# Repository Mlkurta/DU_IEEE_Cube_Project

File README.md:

# DU_IEEE_Cube_Project
Repo for Sharing of files, templates and code for an 8x8x8 RGB LED cube

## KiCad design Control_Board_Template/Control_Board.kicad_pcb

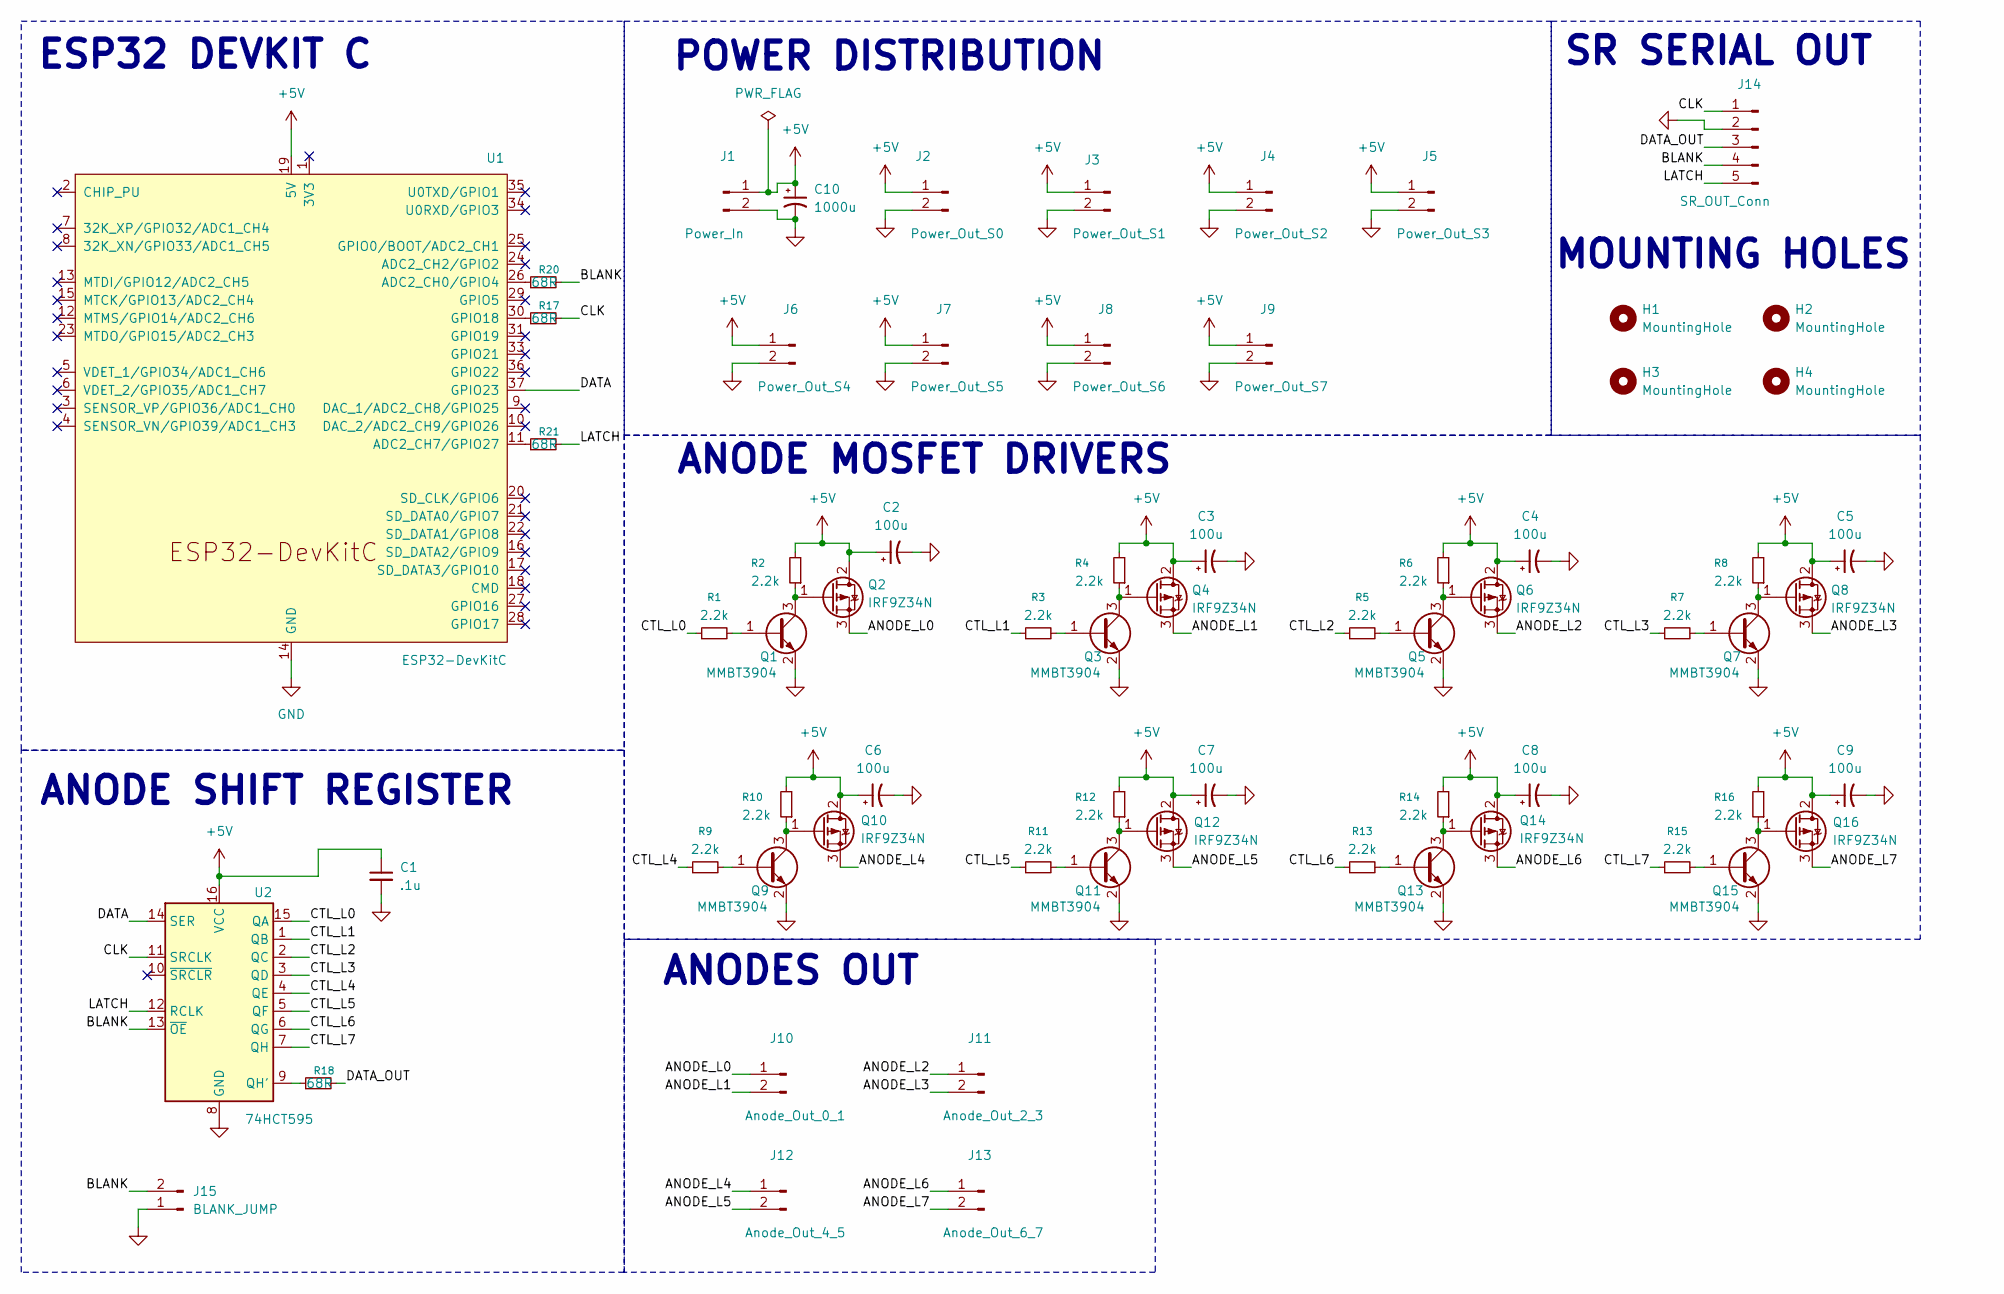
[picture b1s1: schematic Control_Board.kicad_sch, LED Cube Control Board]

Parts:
C1: .1u
C2, C3, C4, C5, C6, C7, C8, C9: 100u; CP_Elec_6.3x7.7; Mfr # 865080545012
C10: 1000u; C_Radial_D10.0mm_H20.0mm_P5.00mm; Mfr # 865080545012
H1, H2, H3, H4: MountingHole; MountingHole_3.2mm_M3
J1: Power_In; JST_VH_B2P-VH_1x02_P3.96mm_Vertical; Mfr # B2P-VH
J2: Power_Out_S0; JST_XH_B2B-XH-A_1x02_P2.50mm_Vertical; Mfr # B2B-XH-A
J3: Power_Out_S1; JST_XH_B2B-XH-A_1x02_P2.50mm_Vertical; Mfr # B2B-XH-A
J4: Power_Out_S2; JST_XH_B2B-XH-A_1x02_P2.50mm_Vertical; Mfr # B2B-XH-A
J5: Power_Out_S3; JST_XH_B2B-XH-A_1x02_P2.50mm_Vertical; Mfr # B2B-XH-A
J6: Power_Out_S4; JST_XH_B2B-XH-A_1x02_P2.50mm_Vertical; Mfr # B2B-XH-A
J7: Power_Out_S5; JST_XH_B2B-XH-A_1x02_P2.50mm_Vertical; Mfr # B2B-XH-A
J8: Power_Out_S6; JST_XH_B2B-XH-A_1x02_P2.50mm_Vertical; Mfr # B2B-XH-A
J9: Power_Out_S7; JST_XH_B2B-XH-A_1x02_P2.50mm_Vertical; Mfr # B2B-XH-A
J10: Anode_Out_0_1; JST_VH_B2P-VH_1x02_P3.96mm_Vertical; Mfr # B2B-XH-A
J11: Anode_Out_2_3; JST_VH_B2P-VH_1x02_P3.96mm_Vertical; Mfr # B2B-XH-A
J12: Anode_Out_4_5; JST_VH_B2P-VH_1x02_P3.96mm_Vertical; Mfr # B2B-XH-A
J13: Anode_Out_6_7; JST_VH_B2P-VH_1x02_P3.96mm_Vertical; Mfr # B2B-XH-A
J14: SR_OUT_Conn; JST_PH_B5B-PH-K_1x05_P2.00mm_Vertical; Mfr # B5B-PH-K-S(LF)(SN)
J15: BLANK_JUMP; PinHeader_1x02_P2.54mm_Vertical
Q1, Q3, Q5, Q7, Q9, Q11, Q13, Q15: MMBT3904; SOT-23; Mfr # MMBT3904-G
Q2, Q4, Q6, Q8, Q10, Q12, Q14, Q16: IRF9Z34N; TO-220-3_Vertical; Mfr # IRF9Z34NPBF
R1, R2, R3, R4, R5, R6, R7, R8, R9, R10, R11, R12, R13, R14, R15, R16: 2.2k; R_0805_2012Metric_Pad1.20x1.40mm_HandSolder; Mfr # 0805W8J0222T5E
R17, R18, R20, R21: 68R; R_0805_2012Metric_Pad1.20x1.40mm_HandSolder; Mfr # 0805W8J0222T5E
U1: ESP32-DevKitC
U2: 74HCT595; SOIC-16_3.9x9.9mm_P1.27mm; Mfr # SN74HC595DR

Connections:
+5V: C1.1, C2.1, C3.1, C4.1, C5.1, C6.1, C7.1, C8.1, C9.1, C10.1, J1.1, J2.1, J3.1, J4.1, J5.1, J6.1, J7.1, J8.1, J9.1, Q2.2 (D), Q4.2 (D), Q6.2 (D), Q8.2 (D), Q10.2 (D), Q12.2 (D), Q14.2 (D), Q16.2 (D), R2.2, R4.2, R6.2, R8.2, R10.2, R12.2, R14.2, R16.2, U1.19 (5V), U2.16 (VCC)
/ANODE_L0: J10.1, Q2.3 (S)
/ANODE_L1: J10.2, Q4.3 (S)
/ANODE_L2: J11.1, Q6.3 (S)
/ANODE_L3: J11.2, Q8.3 (S)
/ANODE_L4: J12.1, Q10.3 (S)
/ANODE_L5: J12.2, Q12.3 (S)
/ANODE_L6: J13.1, Q14.3 (S)
/ANODE_L7: J13.2, Q16.3 (S)
/BLANK: J14.4, J15.2, R20.2, U2.13 (~OE)
/CLK: J14.1, R17.2, U2.11 (SRCLK)
/CTL_L0: R1.1, U2.15 (QA)
/CTL_L1: R3.1, U2.1 (QB)
/CTL_L2: R5.1, U2.2 (QC)
/CTL_L3: R7.1, U2.3 (QD)
/CTL_L4: R9.1, U2.4 (QE)
/CTL_L5: R11.1, U2.5 (QF)
/CTL_L6: R13.1, U2.6 (QG)
/CTL_L7: R15.1, U2.7 (QH)
/DATA: U1.37 (GPIO23), U2.14 (SER)
/DATA_OUT: J14.3, R18.2
/LATCH: J14.5, R21.2, U2.12 (RCLK)
GND: C1.2, C2.2, C3.2, C4.2, C5.2, C6.2, C7.2, C8.2, C9.2, C10.2, J1.2, J2.2, J3.2, J4.2, J5.2, J6.2, J7.2, J8.2, J9.2, J14.2, J15.1, Q1.2 (E), Q3.2 (E), Q5.2 (E), Q7.2 (E), Q9.2 (E), Q11.2 (E), Q13.2 (E), Q15.2 (E), U1.14 (GND), U1.32 (GND), U1.38 (GND), U2.8 (GND)
unnamed: Q1.1 (B), R1.2
unnamed: Q1.3 (C), Q2.1 (G), R2.1
unnamed: Q3.1 (B), R3.2
unnamed: Q3.3 (C), Q4.1 (G), R4.1
unnamed: Q5.1 (B), R5.2
unnamed: Q5.3 (C), Q6.1 (G), R6.1
unnamed: Q7.1 (B), R7.2
unnamed: Q7.3 (C), Q8.1 (G), R8.1
unnamed: Q9.1 (B), R9.2
unnamed: Q9.3 (C), Q10.1 (G), R10.1
unnamed: Q11.1 (B), R11.2
unnamed: Q11.3 (C), Q12.1 (G), R12.1
unnamed: Q13.1 (B), R13.2
unnamed: Q13.3 (C), Q14.1 (G), R14.1
unnamed: Q15.1 (B), R15.2
unnamed: Q15.3 (C), Q16.1 (G), R16.1
unnamed: R20.1, U1.26 (ADC2_CH0/GPIO4)
unnamed: R21.1, U1.11 (ADC2_CH7/GPIO27)
unnamed: R17.1, U1.30 (GPIO18)
unnamed: R18.1, U2.9 (QH')

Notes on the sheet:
ANODES OUT
ANODE MOSFET DRIVERS
SR SERIAL OUT
ANODE SHIFT REGISTER
MOUNTING HOLES
ESP32 DEVKIT C
POWER DISTRIBUTION

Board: 2 copper layers, 66 parts (0 on the bottom side), 43 nets, no tracks yet.

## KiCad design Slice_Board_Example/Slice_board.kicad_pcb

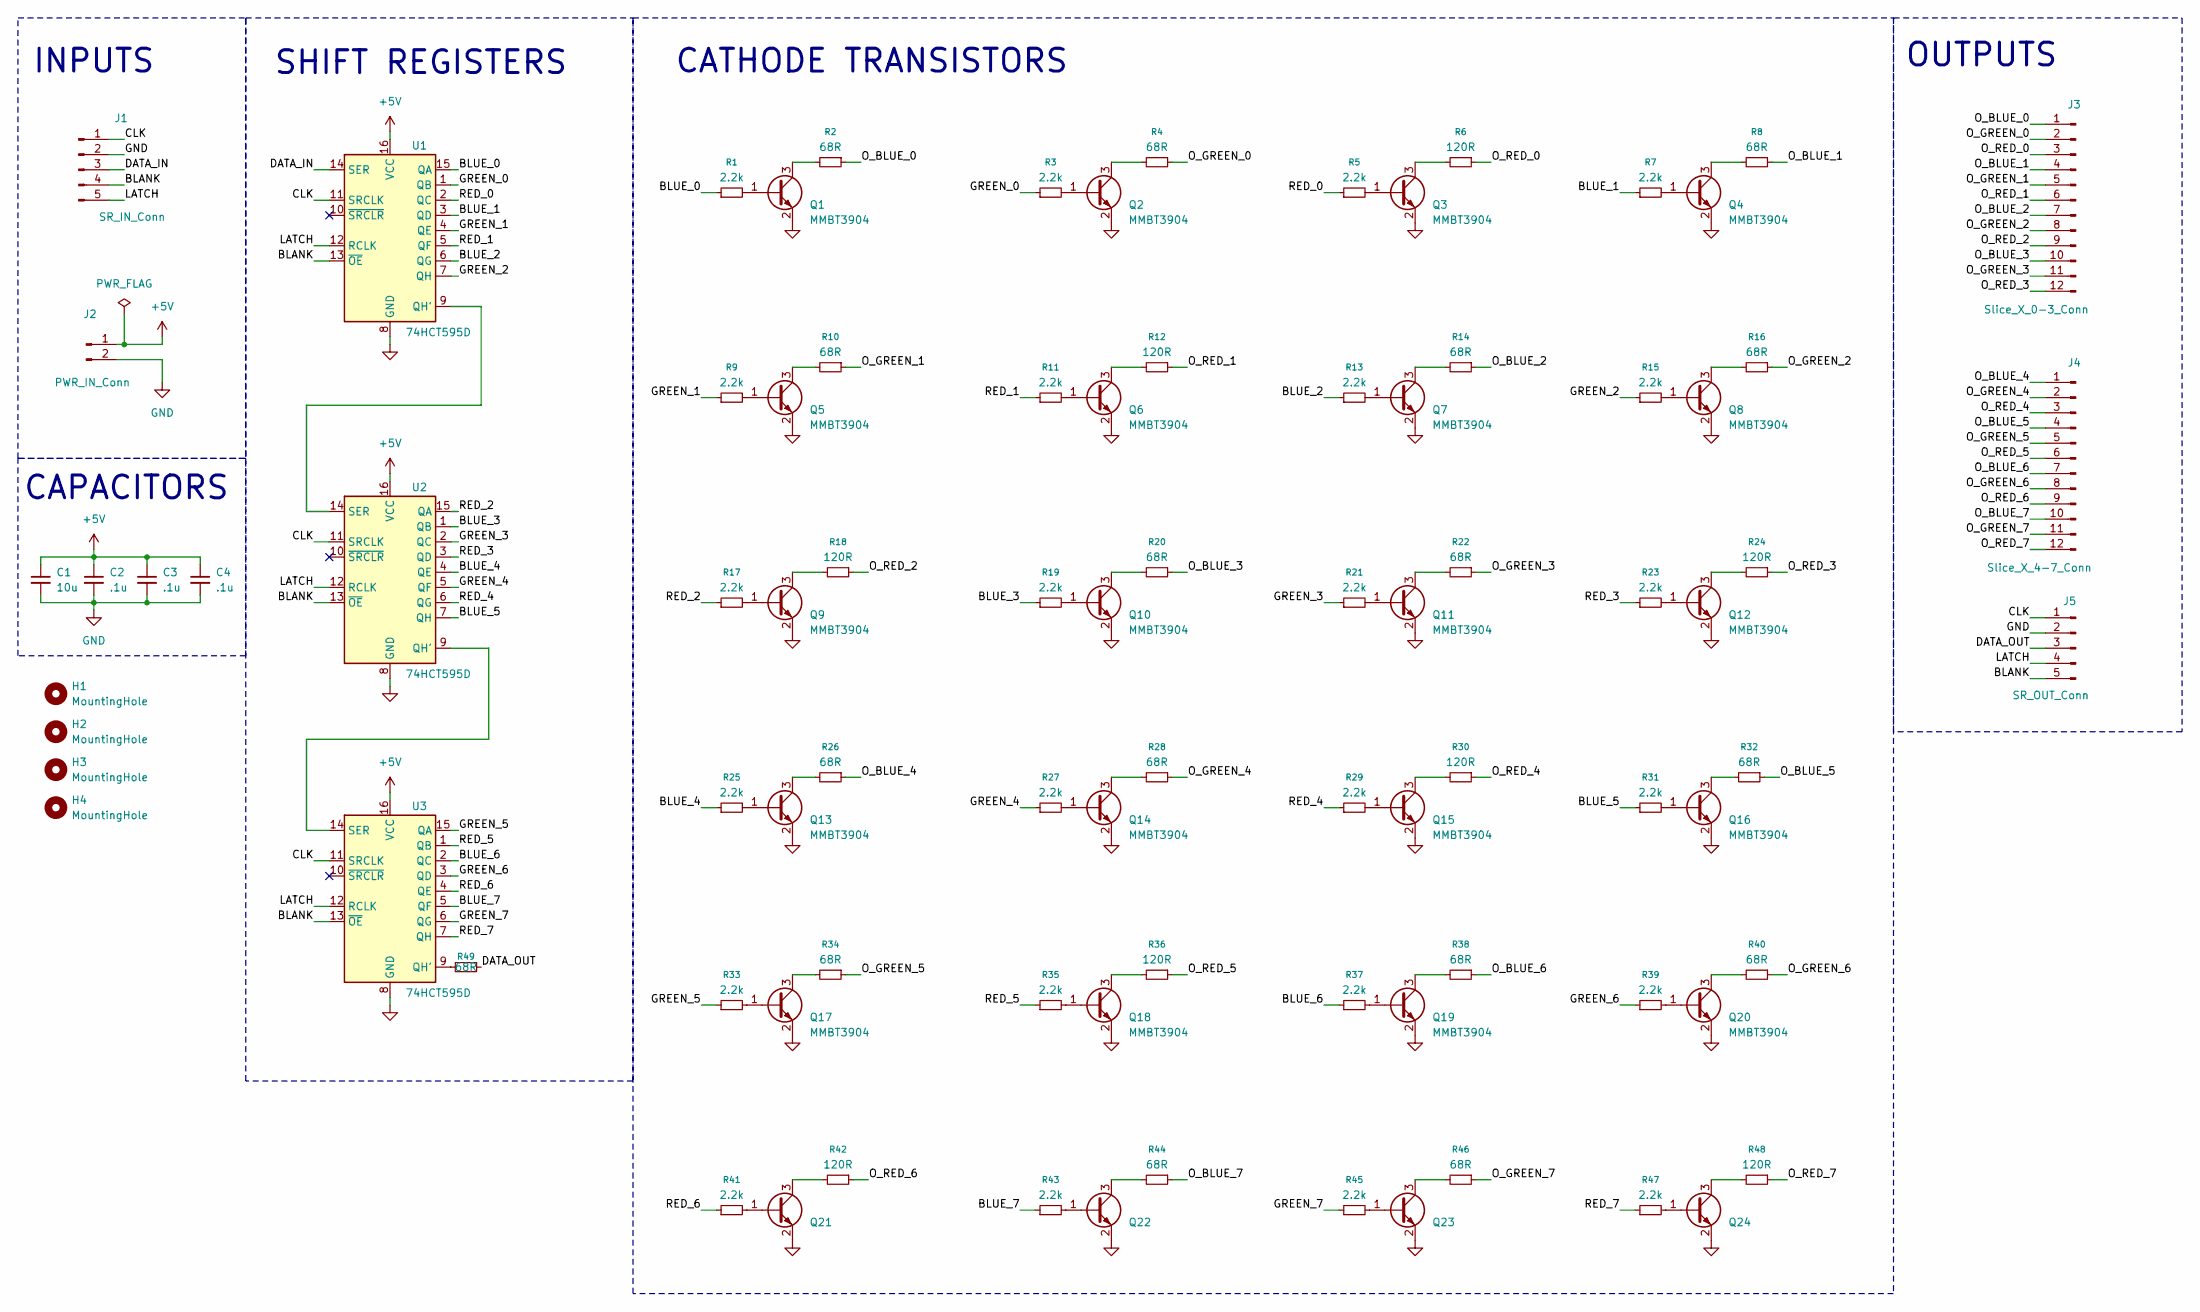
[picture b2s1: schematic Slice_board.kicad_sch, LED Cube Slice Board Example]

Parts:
C1: 10u; C_0805_2012Metric_Pad1.18x1.45mm_HandSolder; Mfr # MCASL21GBB7106KTNA01
C2, C3, C4: .1u; C_0805_2012Metric_Pad1.18x1.45mm_HandSolder; Mfr # KAF21BR71H104JM
H1, H2, H3, H4: MountingHole; MountingHole_3.2mm_M3
J1: SR_IN_Conn; JST_PH_B5B-PH-K_1x05_P2.00mm_Vertical; Mfr # B5B-PH-K-S(LF)(SN)
J2: PWR_IN_Conn; JST_XH_B2B-XH-A_1x02_P2.50mm_Vertical; Mfr # B2B-XH-A
J3: Slice_X_0-3_Conn; JST_PH_B12B-PH-K_1x12_P2.00mm_Vertical; Mfr # B12B-PH-K-S
J4: Slice_X_4-7_Conn; JST_PH_B12B-PH-K_1x12_P2.00mm_Vertical; Mfr # B12B-PH-K-S
J5: SR_OUT_Conn; JST_PH_B5B-PH-K_1x05_P2.00mm_Vertical; Mfr # B5B-PH-K-S(LF)(SN)
Q1, Q2, Q3, Q4, Q5, Q6, Q7, Q8, Q9, Q10, Q11, Q12, Q13, Q14, Q15, Q16, Q17, Q18, Q19, Q20, Q21, Q22, Q23, Q24: MMBT3904; SOT-23; Mfr # 750-MMBT3904-G
R1, R3, R5, R7, R9, R11, R13, R15, R17, R19, R21, R23, R25, R27, R29, R31, R33, R35, R37, R39, R41, R43, R45, R47: 2.2k; R_0805_2012Metric_Pad1.20x1.40mm_HandSolder; Mfr # 0805W8J0222T5E
R2, R4, R8, R10, R14, R16, R20, R22, R26, R28, R32, R34, R38, R40, R44, R46, R49: 68R; R_0805_2012Metric_Pad1.20x1.40mm_HandSolder; Mfr # 0805W8J0680T5E
R6, R12, R18, R24, R30, R36, R42, R48: 120R; R_0805_2012Metric_Pad1.20x1.40mm_HandSolder; Mfr # RT0805FRE13120RL
U1, U2, U3: 74HCT595D; SOIC-16_3.9x9.9mm_P1.27mm; Mfr # 74HCT595D,118

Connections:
+5V: C1.1, C2.1, C3.1, C4.1, J2.1, U1.16 (VCC), U2.16 (VCC), U3.16 (VCC)
/BLANK: J1.4, J5.5, U1.13 (~OE), U2.13 (~OE), U3.13 (~OE)
/BLUE_0: R1.1, U1.15 (QA)
/BLUE_1: R7.1, U1.3 (QD)
/BLUE_2: R13.1, U1.6 (QG)
/BLUE_3: R19.1, U2.1 (QB)
/BLUE_4: R25.1, U2.4 (QE)
/BLUE_5: R31.1, U2.7 (QH)
/BLUE_6: R37.1, U3.2 (QC)
/BLUE_7: R43.1, U3.5 (QF)
/CLK: J1.1, J5.1, U1.11 (SRCLK), U2.11 (SRCLK), U3.11 (SRCLK)
/DATA_IN: J1.3, U1.14 (SER)
/DATA_OUT: J5.3, R49.1
/GREEN_0: R3.1, U1.1 (QB)
/GREEN_1: R9.1, U1.4 (QE)
/GREEN_2: R15.1, U1.7 (QH)
/GREEN_3: R21.1, U2.2 (QC)
/GREEN_4: R27.1, U2.5 (QF)
/GREEN_5: R33.1, U3.15 (QA)
/GREEN_6: R39.1, U3.3 (QD)
/GREEN_7: R45.1, U3.6 (QG)
/LATCH: J1.5, J5.4, U1.12 (RCLK), U2.12 (RCLK), U3.12 (RCLK)
/O_BLUE_0: J3.1, R2.1
/O_BLUE_1: J3.4, R8.1
/O_BLUE_2: J3.7, R14.1
/O_BLUE_3: J3.10, R20.1
/O_BLUE_4: J4.1, R26.1
/O_BLUE_5: J4.4, R32.1
/O_BLUE_6: J4.7, R38.1
/O_BLUE_7: J4.10, R44.1
/O_GREEN_0: J3.2, R4.1
/O_GREEN_1: J3.5, R10.1
/O_GREEN_2: J3.8, R16.1
/O_GREEN_3: J3.11, R22.1
/O_GREEN_4: J4.2, R28.1
/O_GREEN_5: J4.5, R34.1
/O_GREEN_6: J4.8, R40.1
/O_GREEN_7: J4.11, R46.1
/O_RED_0: J3.3, R6.1
/O_RED_1: J3.6, R12.1
/O_RED_2: J3.9, R18.1
/O_RED_3: J3.12, R24.1
/O_RED_4: J4.3, R30.1
/O_RED_5: J4.6, R36.1
/O_RED_6: J4.9, R42.1
/O_RED_7: J4.12, R48.1
/RED_0: R5.1, U1.2 (QC)
/RED_1: R11.1, U1.5 (QF)
/RED_2: R17.1, U2.15 (QA)
/RED_3: R23.1, U2.3 (QD)
/RED_4: R29.1, U2.6 (QG)
/RED_5: R35.1, U3.1 (QB)
/RED_6: R41.1, U3.4 (QE)
/RED_7: R47.1, U3.7 (QH)
GND: C1.2, C2.2, C3.2, C4.2, J1.2, J2.2, J5.2, Q1.2 (E), Q2.2 (E), Q3.2 (E), Q4.2 (E), Q5.2 (E), Q6.2 (E), Q7.2 (E), Q8.2 (E), Q9.2 (E), Q10.2 (E), Q11.2 (E), Q12.2 (E), Q13.2 (E), Q14.2 (E), Q15.2 (E), Q16.2 (E), Q17.2 (E), Q18.2 (E), Q19.2 (E), Q20.2 (E), Q21.2 (E), Q22.2 (E), Q23.2 (E), Q24.2 (E), U1.8 (GND), U2.8 (GND), U3.8 (GND)
unnamed: Q1.1 (B), R1.2
unnamed: Q1.3 (C), R2.2
unnamed: Q2.1 (B), R3.2
unnamed: Q2.3 (C), R4.2
unnamed: Q3.1 (B), R5.2
unnamed: Q3.3 (C), R6.2
unnamed: Q4.1 (B), R7.2
unnamed: Q4.3 (C), R8.2
unnamed: Q5.1 (B), R9.2
unnamed: Q5.3 (C), R10.2
unnamed: Q6.1 (B), R11.2
unnamed: Q6.3 (C), R12.2
unnamed: Q7.1 (B), R13.2
unnamed: Q7.3 (C), R14.2
unnamed: Q8.1 (B), R15.2
unnamed: Q8.3 (C), R16.2
unnamed: Q9.1 (B), R17.2
unnamed: Q9.3 (C), R18.2
unnamed: Q10.1 (B), R19.2
unnamed: Q10.3 (C), R20.2
unnamed: Q11.1 (B), R21.2
unnamed: Q11.3 (C), R22.2
unnamed: Q12.1 (B), R23.2
unnamed: Q12.3 (C), R24.2
unnamed: Q13.1 (B), R25.2
unnamed: Q13.3 (C), R26.2
unnamed: Q14.1 (B), R27.2
unnamed: Q14.3 (C), R28.2
unnamed: Q15.1 (B), R29.2
unnamed: Q15.3 (C), R30.2
unnamed: Q16.1 (B), R31.2
unnamed: Q16.3 (C), R32.2
unnamed: Q17.1 (B), R33.2
unnamed: Q17.3 (C), R34.2
unnamed: Q18.1 (B), R35.2
unnamed: Q18.3 (C), R36.2
unnamed: Q19.1 (B), R37.2
unnamed: Q19.3 (C), R38.2
unnamed: Q20.1 (B), R39.2
unnamed: Q20.3 (C), R40.2
unnamed: Q21.1 (B), R41.2
unnamed: Q21.3 (C), R42.2
unnamed: Q22.1 (B), R43.2
unnamed: Q22.3 (C), R44.2
unnamed: Q23.1 (B), R45.2
unnamed: Q23.3 (C), R46.2
unnamed: Q24.1 (B), R47.2
unnamed: Q24.3 (C), R48.2
unnamed: U1.9 (QH'), U2.14 (SER)
unnamed: U2.9 (QH'), U3.14 (SER)
unnamed: R49.2, U3.9 (QH')

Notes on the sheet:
CATHODE TRANSISTORS
OUTPUTS
SHIFT REGISTERS
INPUTS
CAPACITORS

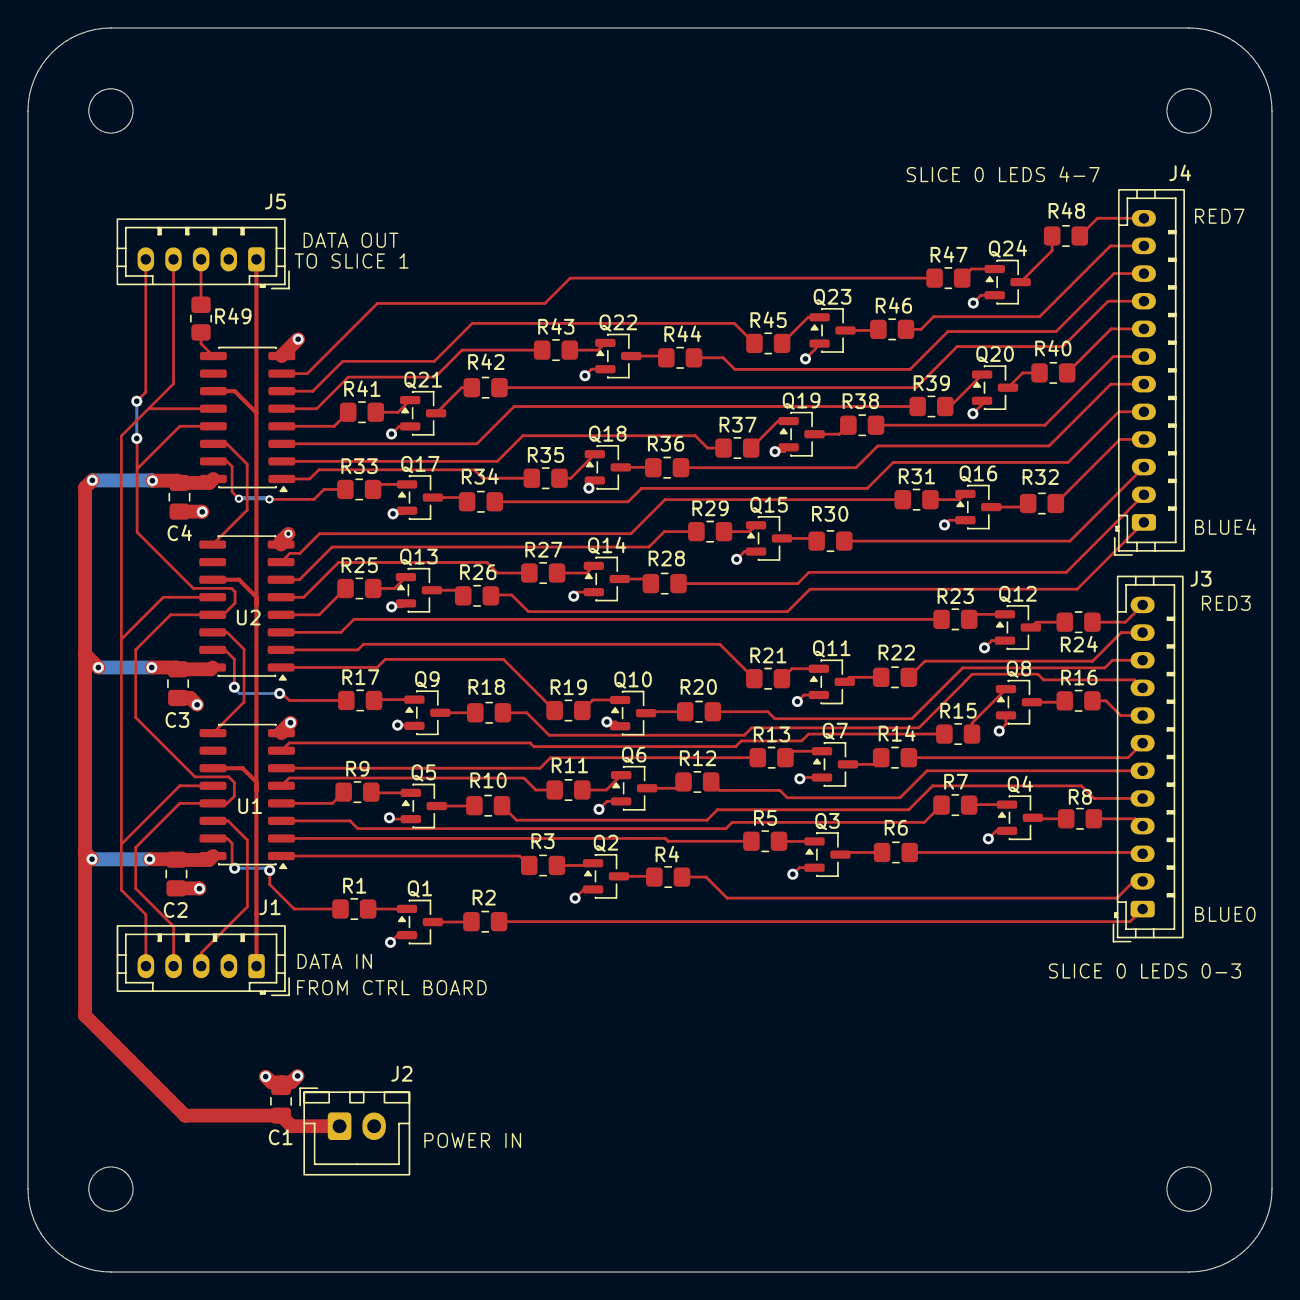
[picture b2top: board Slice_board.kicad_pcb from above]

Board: 2 copper layers, 90.0 x 90.0 mm, 89 parts (0 on the bottom side), 106 nets.

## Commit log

2026-05-02 Add image to Readme.md
